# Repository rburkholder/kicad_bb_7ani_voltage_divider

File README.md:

# BeagleBone Black/Green Cape for Voltage Divider based Analog Input for 7 channels.

* Current version supports thermister and LDR (light dependent resister)
* The book "Exploring BeagleBone®: Tools and Techniques for Building with Embedded Linux®, Second Edition" by Derek Molloy is the source of inspiration
* Relevant Pages include:
  * page 178 - 181 Operational Amplifiers - voltage source, voltage follower, buffer
  * page 248 - 249 Interface Ports
  * page 280 - 282 Analog Inputs, how to read
  * page 282 - 284 unbuffered light meter voltage divider
  * page 420 - 426 buffering analog input
  * page 427 - 431 voltage division & scaling with op-amp included

In effect:
* the two op-amp MCP6002 provides a buffered 1.8V rail-to-rail output for use by the voltage dividers
* the eight op-amp MCP6004 provides a rail-to-rail voltage follower to provide high input impedance for the voltage divider, and low output impedance to the BB analog input pins

Results, as of 2025/12/26 - not etched yet:
* 
* 
* 
  * Two thermisters show the furnace water temperature (hot water exit, cold water return) and a light detecting resistor in the furnace to detect flame.  
    * it shows the lag times of a) hot water heating the pipe which the hot water thermister detects, and b) some lag for the water to cool and cycle back to the cold return of the furnace (values are unscaled 0-4095)
  * The aquastat controls when the flame is on based upon a) at least one thermostat is calling for hot water, and b) the water needs to be brought back to temperature
  * The UPS furnace runtime is a delegate way to determine how much work the water pump is performing - the more valves opened, the more water to push, the more energy required (UPS runtime reduces due to higher power demanded).

The whole reason for this configuration is due to this being an older system and the natural gas valve has recently had a tendency to stick open, which causes the water to overheat.  This is my interim way to detect when the furnace does not turn off and I have a minute or two to tap the valve so that it closes.  A replacement is supposed to be on its way.

Contributing projects:
* [ad2mqtt](https://github.com/rburkholder/ad2mqtt) - reads the BeagleBone Analog Inputs and publishes to an MQTT message broker
* [apparition](https://github.com/rburkholder/apparition) - a home monitoring and automation solution focussing on LUA scripting
  * [analog_in.lua](https://github.com/rburkholder/apparition/blob/master/var/script/analog_in.lua) - subscribes to the analog values, checks limits, and issues telegram messages while the water temperature rises above a limit

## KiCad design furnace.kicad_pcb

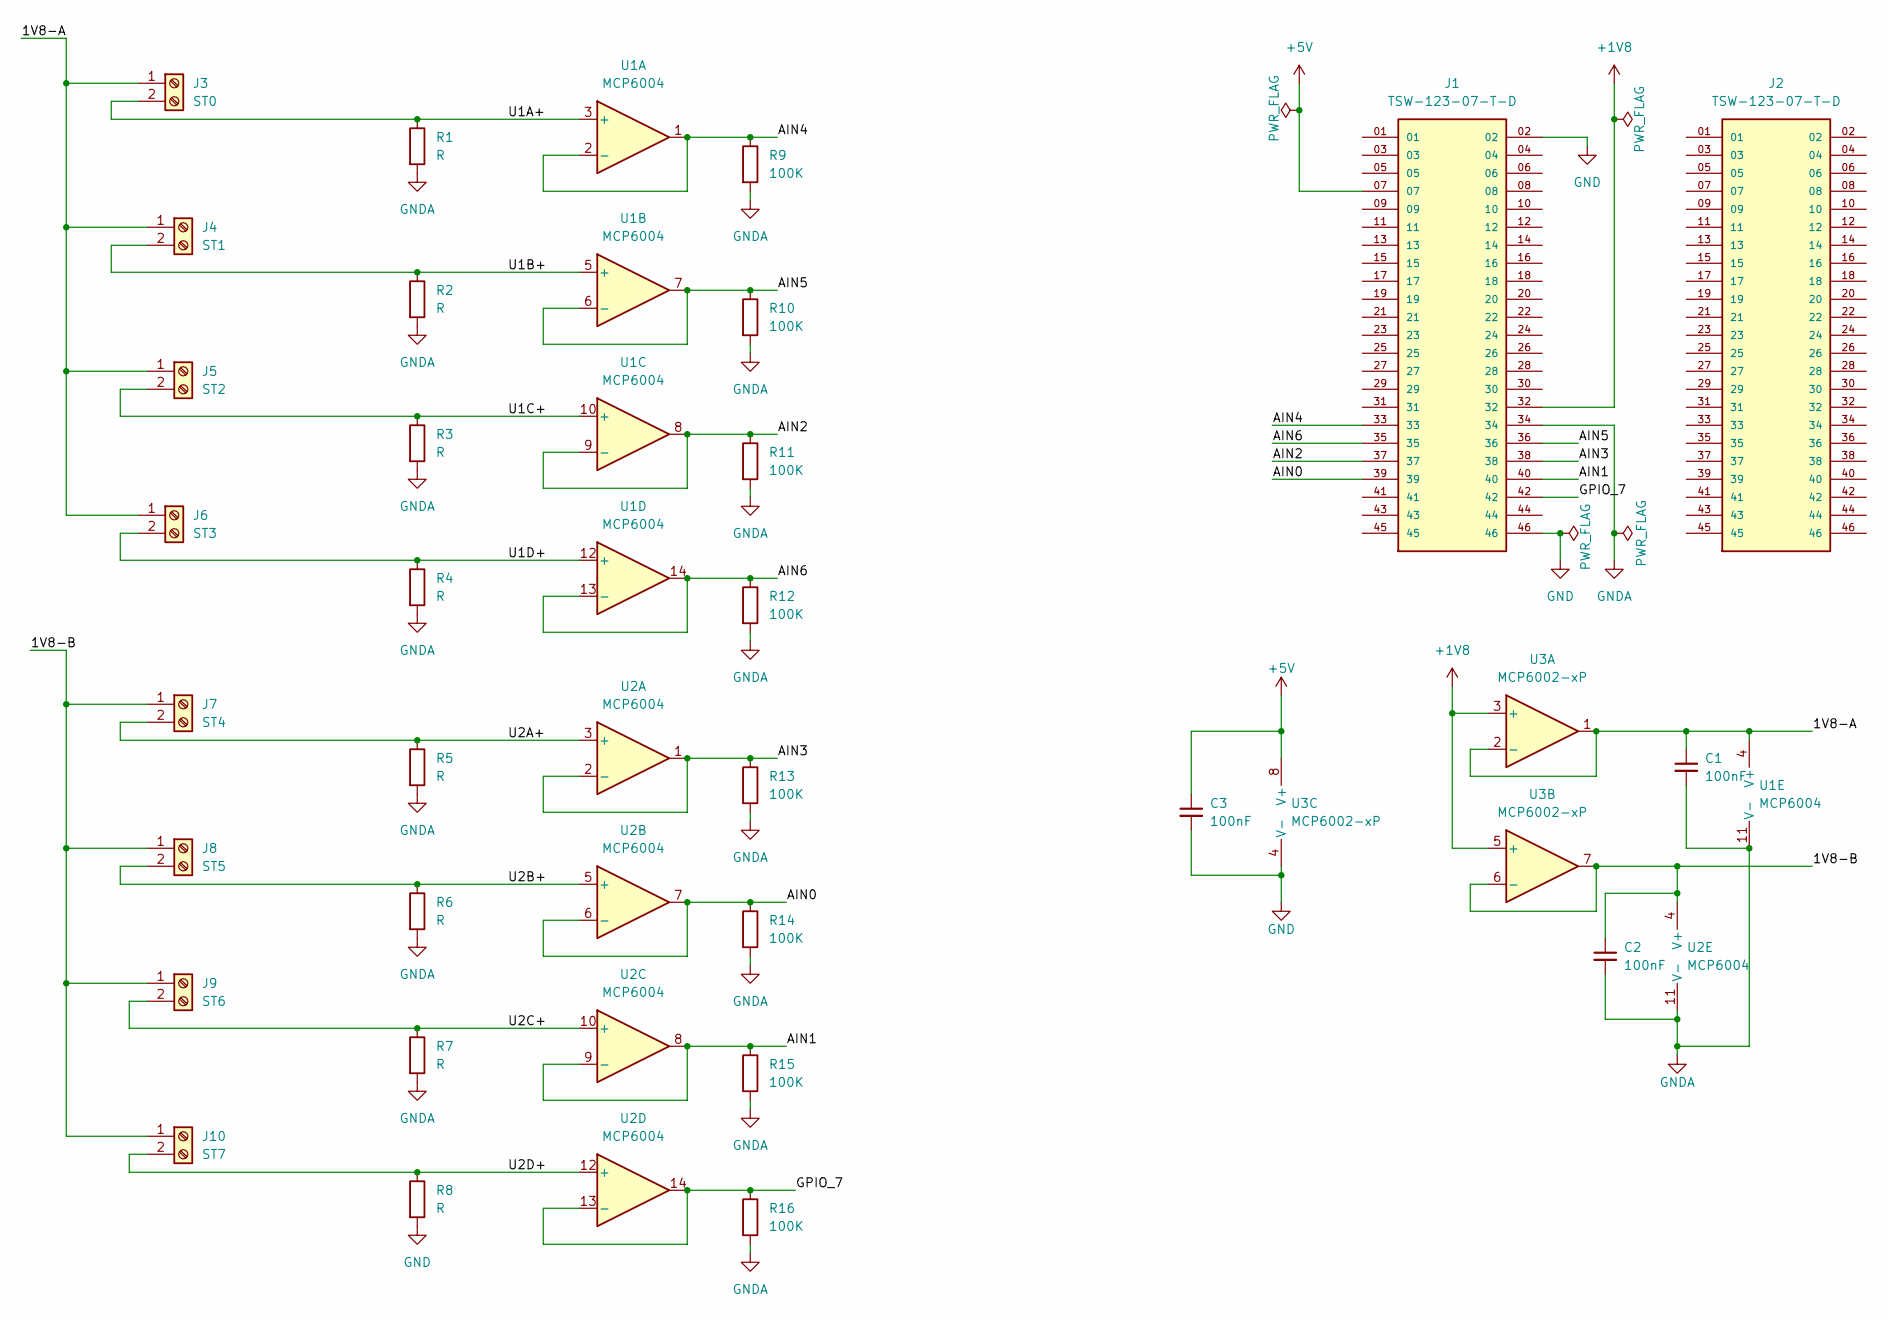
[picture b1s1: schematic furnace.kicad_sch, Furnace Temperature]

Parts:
C1, C2, C3: 100nF; C_Disc_D4.7mm_W2.5mm_P5.00mm
J1, J2: TSW-123-07-T-D; SAMTEC_TSW-123-07-T-D; PARTREV R
J3: ST0; CONN_1728284_PXC
J4: ST1; CONN_1728284_PXC
J5: ST2; CONN_1728284_PXC
J6: ST3; CONN_1728284_PXC
J7: ST4; CONN_1728284_PXC
J8: ST5; CONN_1728284_PXC
J9: ST6; CONN_1728284_PXC
J10: ST7; CONN_1728284_PXC
R1, R2, R3, R4, R5, R6, R7, R8: R; R_Axial_DIN0207_L6.3mm_D2.5mm_P10.16mm_Horizontal
R9, R10, R11, R12, R13, R14, R15, R16: 100K; R_Axial_DIN0207_L6.3mm_D2.5mm_P10.16mm_Horizontal
U1, U2: MCP6004; DIP-14_W7.62mm
U3: MCP6002-xP; DIP-8_W7.62mm

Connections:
+1V8: J1.32, U3.3 (+), U3.5 (+)
+5V: C3.1, J1.07, U3.8 (V+)
/1V8-A: C1.1, J3.1, J4.1, J5.1, J6.1, U1.4 (V+), U3.1, U3.2 (-)
/1V8-B: C2.1, J7.1, J8.1, J9.1, J10.1, U2.4 (V+), U3.6 (-), U3.7
/AIN0: J1.39, R14.1, U2.6 (-), U2.7
/AIN1: J1.40, R15.1, U2.8, U2.9 (-)
/AIN2: J1.37, R11.1, U1.8, U1.9 (-)
/AIN3: J1.38, R13.1, U2.1, U2.2 (-)
/AIN4: J1.33, R9.1, U1.1, U1.2 (-)
/AIN5: J1.36, R10.1, U1.6 (-), U1.7
/AIN6: J1.35, R12.1, U1.13 (-), U1.14
/GPIO_7: J1.42, R16.1, U2.13 (-), U2.14
/U1A+: J3.2, R1.1, U1.3 (+)
/U1B+: J4.2, R2.1, U1.5 (+)
/U1C+: J5.2, R3.1, U1.10 (+)
/U1D+: J6.2, R4.1, U1.12 (+)
/U2A+: J7.2, R5.1, U2.3 (+)
/U2B+: J8.2, R6.1, U2.5 (+)
/U2C+: J9.2, R7.1, U2.10 (+)
/U2D+: J10.2, R8.1, U2.12 (+)
GND: C3.2, J1.02, J1.46, R8.2, U3.4 (V-)
GNDA: C1.2, C2.2, J1.34, R1.2, R2.2, R3.2, R4.2, R5.2, R6.2, R7.2, R9.2, R10.2, R11.2, R12.2, R13.2, R14.2, R15.2, R16.2, U1.11 (V-), U2.11 (V-)

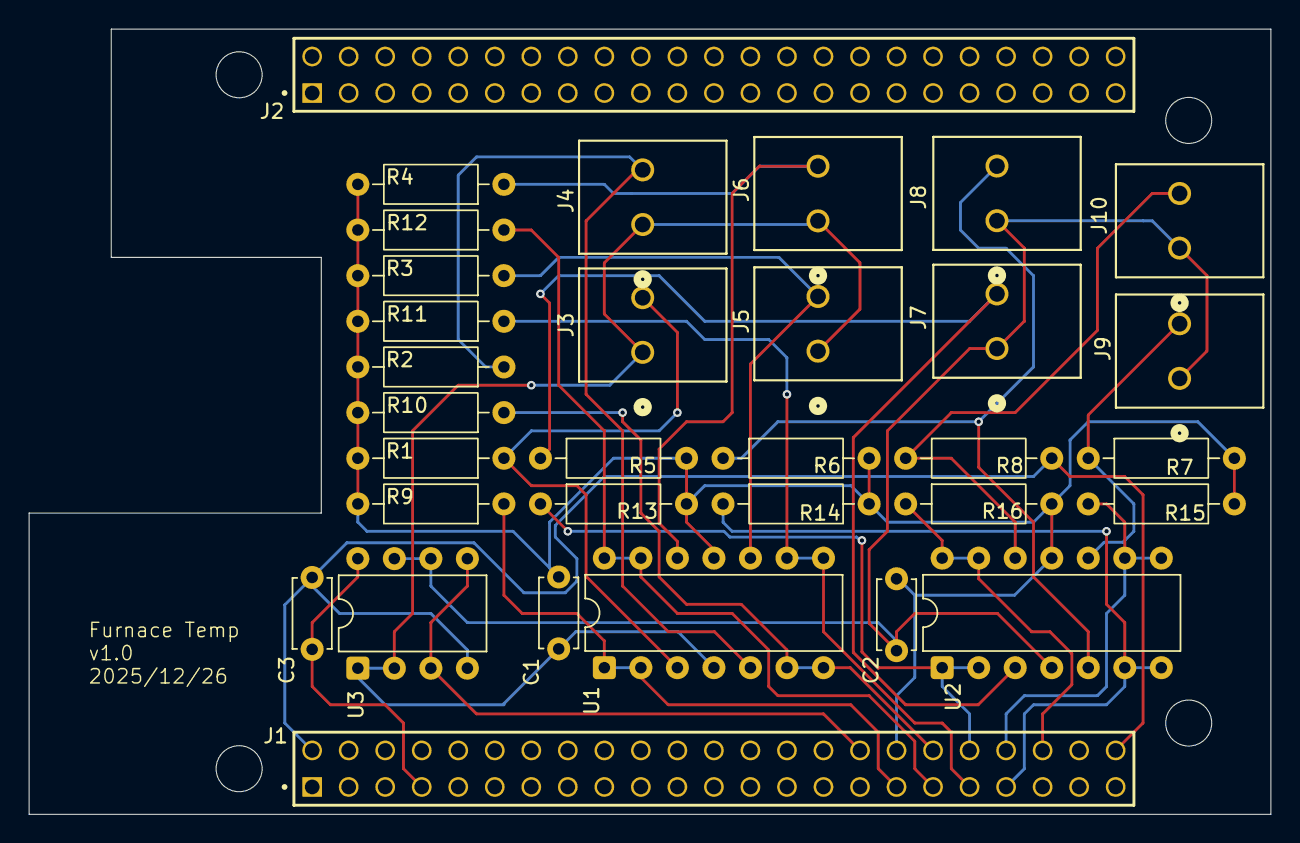
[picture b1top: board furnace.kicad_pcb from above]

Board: 2 copper layers, 86.4 x 54.6 mm, 32 parts (0 on the bottom side), 22 nets.

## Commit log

2025-12-27 furnace - current state schematic/pcb
2025-12-27 fp-lib-table - add library components
2025-12-27 README.md - background info for the design
2025-12-27 README.md - screenshots
2025-12-27 README.md - add rationale for project
2025-12-27 furnace.kicad_sch - update schematic description
2025-12-27 furnace.kicad_sch - add sensor references
2025-12-27 furnace.kicad_sch - terminal block and header strip info
